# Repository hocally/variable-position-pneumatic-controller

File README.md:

# variable-position-pneumatic-controller
The goal of this project is to achieve variable position control of a pneumatic cylinder using closed-loop feedback via a bidirectional solenoid valve, a pneumatic cylinder, a string potentiometer, limit switches, and an Arduino Nano with supporting control circuitry. If this project is successful, it will be ported over to Java for use on an FRC RoboRio.

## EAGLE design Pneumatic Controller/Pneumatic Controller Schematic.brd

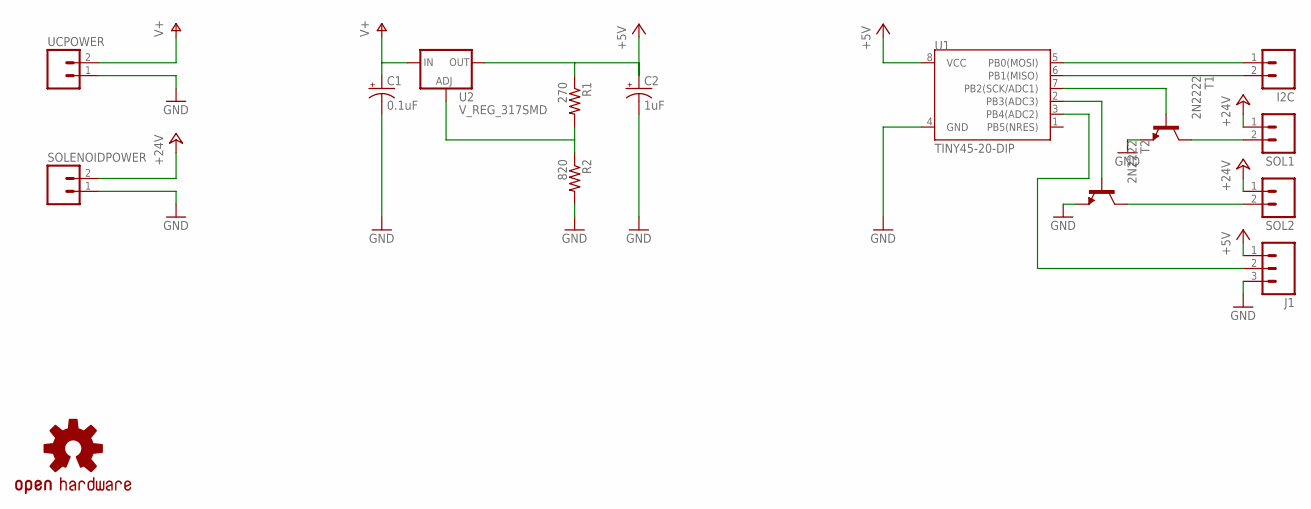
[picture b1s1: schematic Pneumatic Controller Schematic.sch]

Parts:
C1: 0.1uF; CPOL-RADIAL-10UF-25V
C2: 1uF; CPOL-RADIAL-10UF-25V
I2C: M02PTH; 1X02
J1: M03PTH; 1X03
LOGO1: OSHW-LOGOS-COPPER; OSHW-LOGO-S_COPPER
R1: 270; AXIAL-0.4
R2: 820; AXIAL-0.4
SOL1, SOL2: M02PTH; 1X02
SOLENOIDPOWER: M02PTH; 1X02
T1, T2: 2N2222; TO92-EBC-OVAL
U1: TINY45-20-DIP; DIP08
U2: V_REG_317SMD; SOT223
UCPOWER: M02PTH; 1X02

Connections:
+5V: C2.1 (+), J1.1, R1.P$1 (1), U1.8 (VCC), U2.2 (OUT)
+12V: UCPOWER.2
+24V: SOL1.1, SOL2.1, SOLENOIDPOWER.2
GND: C1.2 (-), C2.2 (-), J1.3, R2.P$2 (2), SOLENOIDPOWER.1, T1.E, T2.E, U1.4 (GND), UCPOWER.1
unnamed: R1.P$2 (2), R2.P$1 (1), U2.1 (ADJ)
unnamed: I2C.1, U1.5 (PB0(MOSI))
unnamed: I2C.2, U1.6 (PB1(MISO))
unnamed: T1.B, U1.7 (PB2(SCK/ADC1))
unnamed: T2.B, U1.2 (PB3(ADC3))
unnamed: SOL1.2, T1.C
unnamed: SOL2.2, T2.C
unnamed: J1.2, U1.3 (PB4(ADC2))
V+: C1.1 (+), U2.3 (IN)

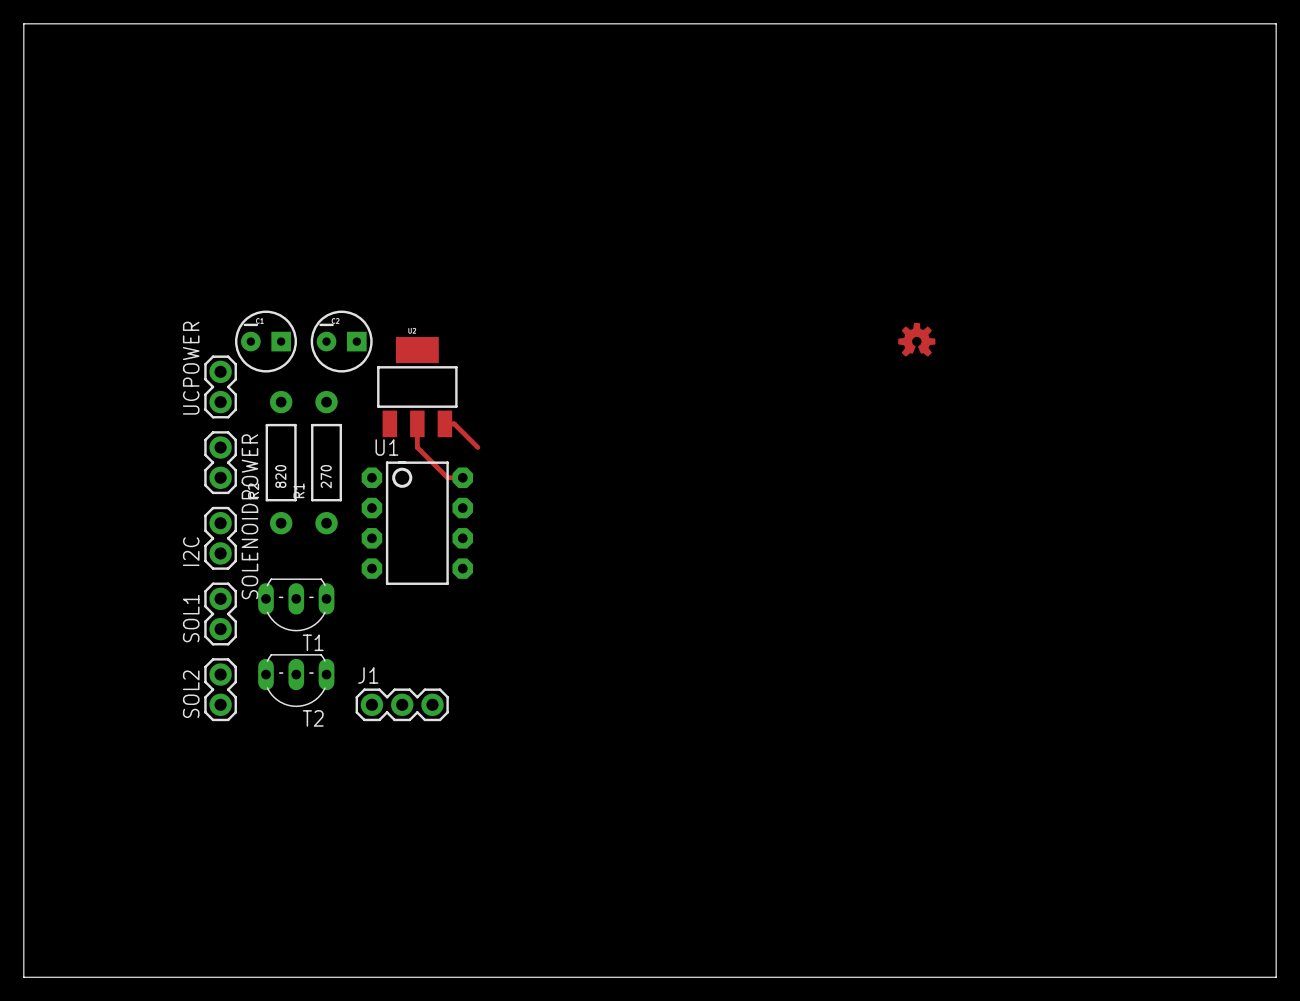
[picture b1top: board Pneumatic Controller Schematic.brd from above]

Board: 2 copper layers, 105.1 x 80.0 mm, 15 parts (0 on the bottom side), 12 nets.

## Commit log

2016-08-22 Update README.md
    Bad at spelling
2016-08-22 Add files via upload
    This is the first revision of the project.
2016-08-31 Add files via upload
    Eagle Board Files

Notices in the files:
parts and their libraries:
SparkFun-Capacitors: Licensing: Creative Commons ShareAlike 4.0 International - https://creativecommons.org/licenses/by-sa/4.0
